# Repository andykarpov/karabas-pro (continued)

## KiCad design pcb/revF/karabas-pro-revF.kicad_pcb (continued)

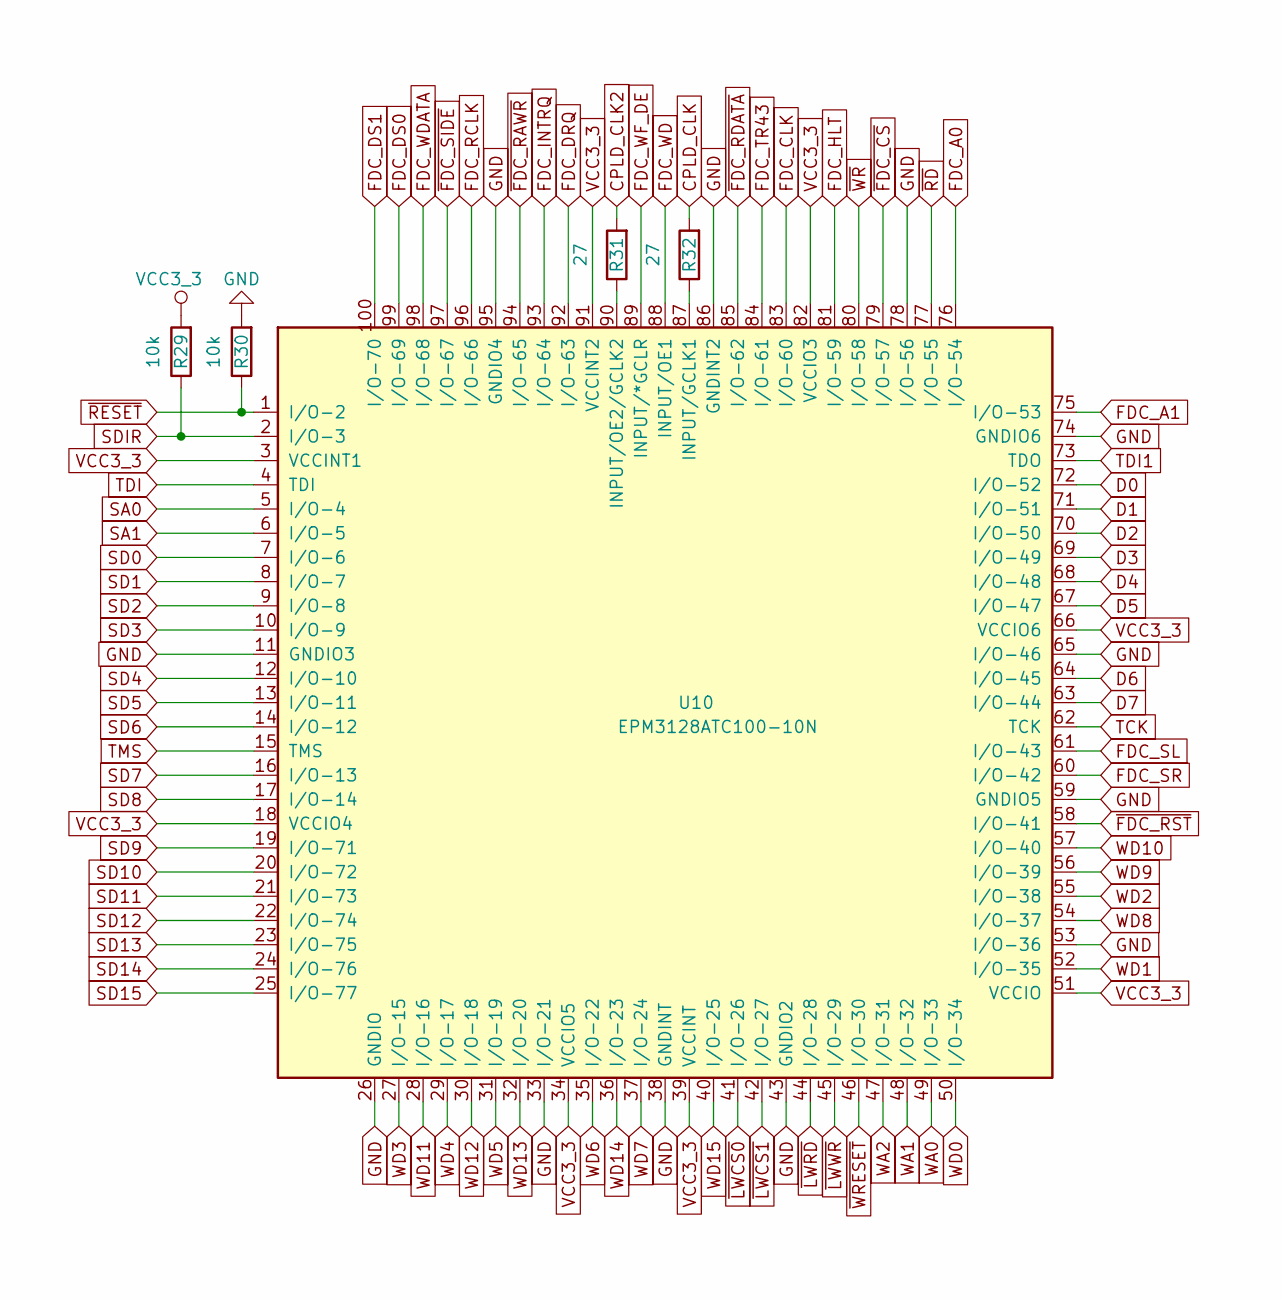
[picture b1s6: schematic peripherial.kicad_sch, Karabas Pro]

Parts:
R29, R30: 10k; R_0805_2012Metric_Pad1.20x1.40mm_HandSolder
R31, R32: 27; R_0805_2012Metric_Pad1.20x1.40mm_HandSolder
U10: EPM3128ATC100-10N; LQFP-100_14x14mm_P0.5mm

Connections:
CPLD_CLK: R32.2; also elsewhere on the board
CPLD_CLK2: R31.2; also elsewhere on the board
D0: U10.72 (I/O-52); also elsewhere on the board
D1: U10.71 (I/O-51); also elsewhere on the board
D2: U10.70 (I/O-50); also elsewhere on the board
D3: U10.69 (I/O-49); also elsewhere on the board
D4: U10.68 (I/O-48); also elsewhere on the board
D5: U10.67 (I/O-47); also elsewhere on the board
D6: U10.64 (I/O-45); also elsewhere on the board
D7: U10.63 (I/O-44); also elsewhere on the board
FDC_A0: U10.76 (I/O-54); also elsewhere on the board
FDC_A1: U10.75 (I/O-53); also elsewhere on the board
FDC_CLK: U10.83 (I/O-60); also elsewhere on the board
FDC_DRQ: U10.92 (I/O-63); also elsewhere on the board
FDC_DS0: U10.99 (I/O-69); also elsewhere on the board
FDC_DS1: U10.100 (I/O-70); also elsewhere on the board
FDC_HLT: U10.81 (I/O-59); also elsewhere on the board
FDC_INTRQ: U10.93 (I/O-64); also elsewhere on the board
FDC_RCLK: U10.96 (I/O-66); also elsewhere on the board
FDC_SL: U10.61 (I/O-43); also elsewhere on the board
FDC_SR: U10.60 (I/O-42); also elsewhere on the board
FDC_TR43: U10.84 (I/O-61); also elsewhere on the board
FDC_WD: U10.88 (INPUT/OE1); also elsewhere on the board
FDC_WDATA: U10.98 (I/O-68); also elsewhere on the board
FDC_WF_DE: U10.89 (INPUT/*GCLR); also elsewhere on the board
GND: R30.2, U10.11 (GNDIO3), U10.26 (GNDIO), U10.33 (I/O-21), U10.38 (GNDINT), U10.43 (GNDIO2), U10.53 (I/O-36), U10.59 (GNDIO5), U10.65 (I/O-46), U10.74 (GNDIO6), U10.78 (I/O-56), U10.86 (GNDINT2), U10.95 (GNDIO4); also elsewhere on the board
unnamed: R32.1, U10.87 (INPUT/GCLK1)
unnamed: R31.1, U10.90 (INPUT/OE2/GCLK2)
SA0: U10.5 (I/O-4); also elsewhere on the board
SA1: U10.6 (I/O-5); also elsewhere on the board
SD0: U10.7 (I/O-6); also elsewhere on the board
SD1: U10.8 (I/O-7); also elsewhere on the board
SD2: U10.9 (I/O-8); also elsewhere on the board
SD3: U10.10 (I/O-9); also elsewhere on the board
SD4: U10.12 (I/O-10); also elsewhere on the board
SD5: U10.13 (I/O-11); also elsewhere on the board
SD6: U10.14 (I/O-12); also elsewhere on the board
SD7: U10.16 (I/O-13); also elsewhere on the board
SD8: U10.17 (I/O-14); also elsewhere on the board
SD9: U10.19 (I/O-71); also elsewhere on the board
SD10: U10.20 (I/O-72); also elsewhere on the board
SD11: U10.21 (I/O-73); also elsewhere on the board
SD12: U10.22 (I/O-74); also elsewhere on the board
SD13: U10.23 (I/O-75); also elsewhere on the board
SD14: U10.24 (I/O-76); also elsewhere on the board
SD15: U10.25 (I/O-77); also elsewhere on the board
SDIR: R29.1, U10.2 (I/O-3); also elsewhere on the board
TCK: U10.62 (TCK); also elsewhere on the board
TDI: U10.4 (TDI); also elsewhere on the board
TDI1: U10.73 (TDO); also elsewhere on the board
TMS: U10.15 (TMS); also elsewhere on the board
VCC3_3: R29.2, U10.3 (VCCINT1), U10.18 (VCCIO4), U10.34 (VCCIO5), U10.39 (VCCINT), U10.51 (VCCIO), U10.66 (VCCIO6), U10.82 (VCCIO3), U10.91 (VCCINT2); also elsewhere on the board
WA0: U10.49 (I/O-33); also elsewhere on the board
WA1: U10.48 (I/O-32); also elsewhere on the board
WA2: U10.47 (I/O-31); also elsewhere on the board
WD0: U10.50 (I/O-34); also elsewhere on the board
WD1: U10.52 (I/O-35); also elsewhere on the board
WD2: U10.55 (I/O-38); also elsewhere on the board
WD3: U10.27 (I/O-15); also elsewhere on the board
WD4: U10.29 (I/O-17); also elsewhere on the board
WD5: U10.31 (I/O-19); also elsewhere on the board
WD6: U10.35 (I/O-22); also elsewhere on the board
WD7: U10.37 (I/O-24); also elsewhere on the board
WD8: U10.54 (I/O-37); also elsewhere on the board
WD9: U10.56 (I/O-39); also elsewhere on the board
WD10: U10.57 (I/O-40); also elsewhere on the board
WD11: U10.28 (I/O-16); also elsewhere on the board
WD12: U10.30 (I/O-18); also elsewhere on the board
WD13: U10.32 (I/O-20); also elsewhere on the board
WD14: U10.36 (I/O-23); also elsewhere on the board
WD15: U10.40 (I/O-25); also elsewhere on the board
~FDC_CS: U10.79 (I/O-57); also elsewhere on the board
~FDC_RAWR: U10.94 (I/O-65); also elsewhere on the board
~FDC_RDATA: U10.85 (I/O-62); also elsewhere on the board
~FDC_RST: U10.58 (I/O-41); also elsewhere on the board
~FDC_SIDE: U10.97 (I/O-67); also elsewhere on the board
~LWCS0: U10.41 (I/O-26); also elsewhere on the board
~LWCS1: U10.42 (I/O-27); also elsewhere on the board
~LWRD: U10.44 (I/O-28); also elsewhere on the board
~LWWR: U10.45 (I/O-29); also elsewhere on the board
~RD: U10.77 (I/O-55); also elsewhere on the board
~RESET: R30.1, U10.1 (I/O-2); also elsewhere on the board
~WRESET: U10.46 (I/O-30); also elsewhere on the board
~WR: U10.80 (I/O-58); also elsewhere on the board

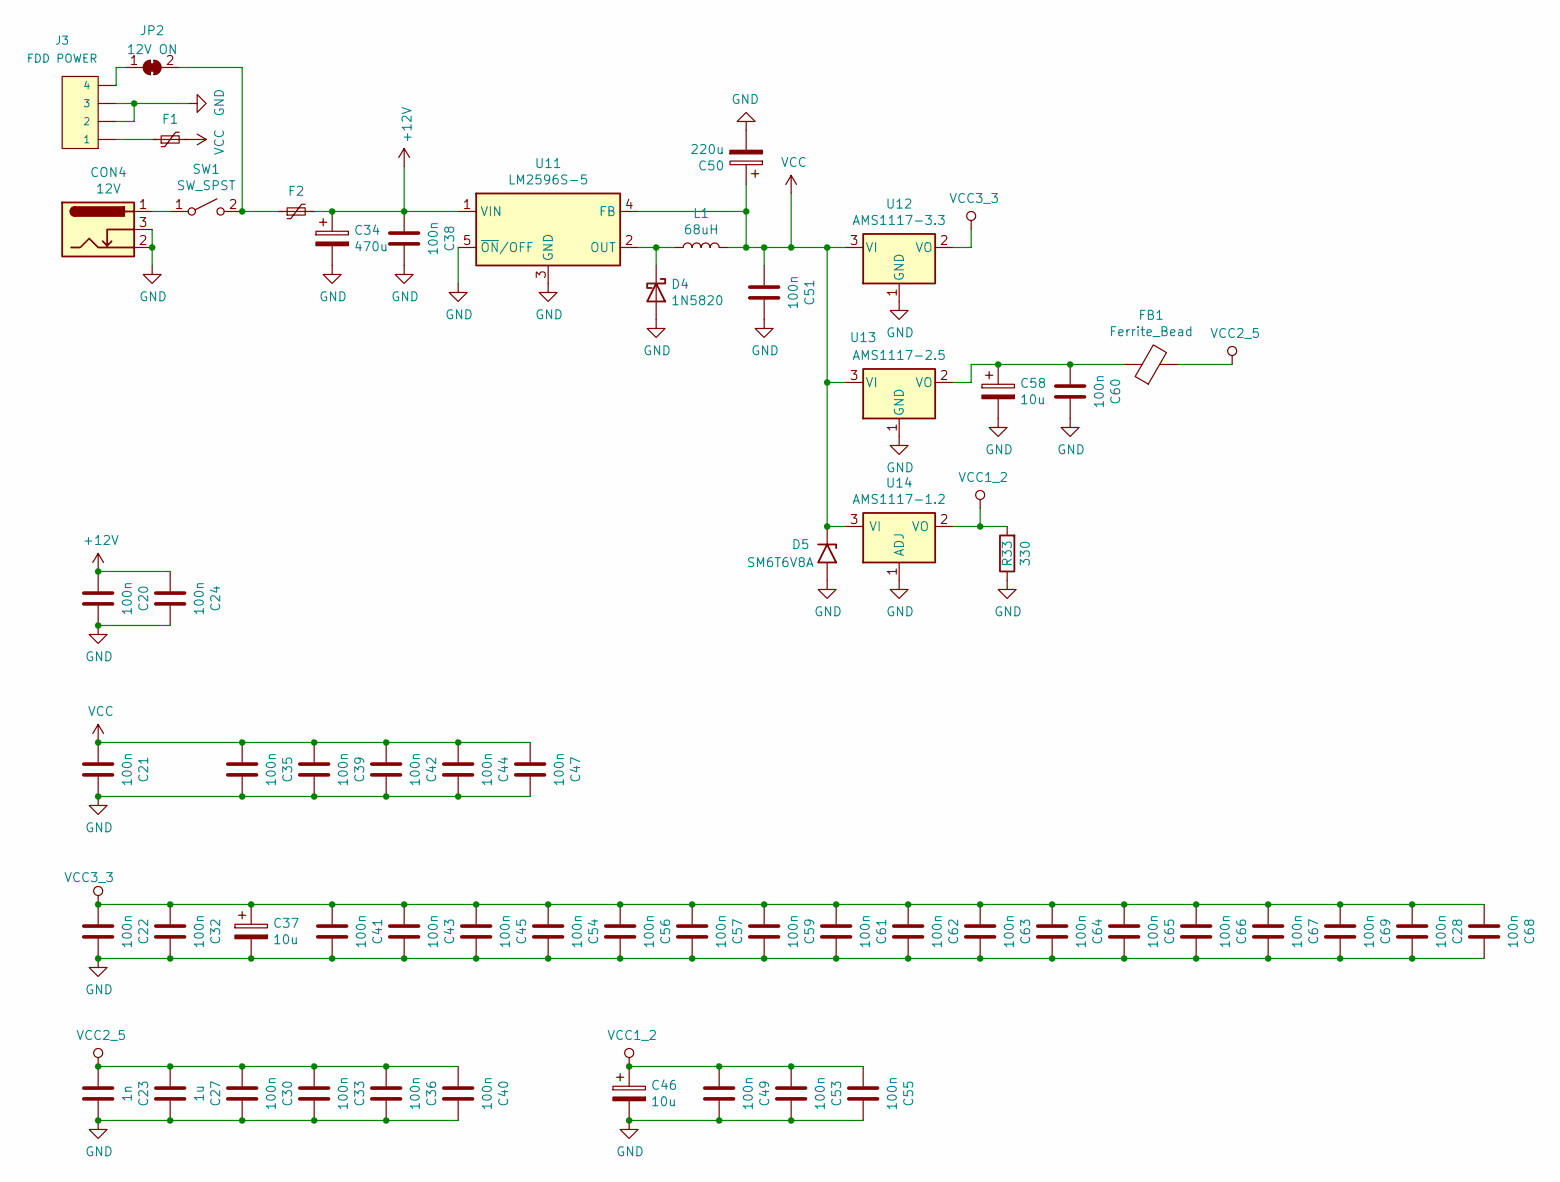
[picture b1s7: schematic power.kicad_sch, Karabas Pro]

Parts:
C20, C21, C22, C24, C28, C30, C32, C33, C35, C36, C38, C39, C40, C41, C42, C43, C44, C45, C47, C49, C51, C53, C54, C55, C56, C57, C59, C60, C61, C62, C63, C64, C65, C66, C67, C68, C69: 100n; C_0805_2012Metric_Pad1.18x1.45mm_HandSolder
C23: 1n; C_0805_2012Metric_Pad1.18x1.45mm_HandSolder
C27: 1u; C_0805_2012Metric_Pad1.18x1.45mm_HandSolder
C34: 470u; CP_Radial_D8.0mm_P3.80mm
C37, C46, C58: 10u; CP_EIA-7343-31_Kemet-D-uni
C50: 220u; CP_Radial_D7.5mm_P2.50mm
CON4: 12V; BarrelJack_Wuerth_6941xx301002
D4: 1N5820; D_DO-201AD_P15.24mm_Horizontal
D5: SM6T6V8A; D_SMB_Handsoldering
F1, F2: Polyfuse_Small; Fuse_1812_4532Metric_Pad1.30x3.40mm_HandSolder
FB1: Ferrite_Bead; L_0805_2012Metric_Pad1.15x1.40mm_HandSolder
J3: FDD POWER; PinHeader_1x04_P2.54mm_Vertical
JP2: 12V ON; SolderJumper-2_P1.3mm_Bridged_Pad1.0x1.5mm
L1: 68uH; L_12x12mm_H6mm
R33: 330; R_0805_2012Metric_Pad1.20x1.40mm_HandSolder
SW1: SW_SPST; SW_Slide_SPDT_Angled_CK_OS102011MA1Q
U11: LM2596S-5; TO-263-5_TabPin3
U12: AMS1117-3.3; TO-252-2
U13: AMS1117-2.5; SOT-223-3_TabPin2
U14: AMS1117-1.2; SOT-223-3_TabPin2

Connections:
+12V: C20.1, C24.1, C34.1, C38.1, F2.2, U11.1 (VIN); also elsewhere on the board
GND: C20.2, C21.2, C22.2, C23.2, C24.2, C27.2, C28.2, C30.2, C32.2, C33.2, C34.2, C35.2, C36.2, C37.2, C38.2, C39.2, C40.2, C41.2, C42.2, C43.2, C44.2, C45.2, C46.2, C47.2, C49.2, C50.2, C51.2, C53.2, C54.2, C55.2, C56.2, C57.2, C58.2, C59.2, C60.2, C61.2, C62.2, C63.2, C64.2, C65.2, C66.2, C67.2, C68.2, C69.2, CON4.2, CON4.3, D4.2 (A), D5.2 (A2), J3.2, J3.3, R33.1, U11.3 (GND), U11.5 (~ON/OFF), U12.1 (GND), U13.1 (GND), U14.1 (ADJ); also elsewhere on the board
unnamed: D4.1 (K), L1.1, U11.2 (OUT)
unnamed: F1.1, J3.1
unnamed: J3.4, JP2.1 (A)
unnamed: F2.1, JP2.2 (B), SW1.2 (B)
unnamed: CON4.1, SW1.1 (A)
unnamed: C58.1, C60.1, FB1.1, U13.2 (VO)
VCC: C21.1, C35.1, C39.1, C42.1, C44.1, C47.1, C50.1, C51.1, D5.1 (A1), F1.2, L1.2, U11.4 (FB), U12.3 (VI), U13.3 (VI), U14.3 (VI); also elsewhere on the board
VCC1_2: C46.1, C49.1, C53.1, C55.1, R33.2, U14.2 (VO); also elsewhere on the board
VCC2_5: C23.1, C27.1, C30.1, C33.1, C36.1, C40.1, FB1.2; also elsewhere on the board
VCC3_3: C22.1, C28.1, C32.1, C37.1, C41.1, C43.1, C45.1, C54.1, C56.1, C57.1, C59.1, C61.1, C62.1, C63.1, C64.1, C65.1, C66.1, C67.1, C68.1, C69.1, U12.2 (VO); also elsewhere on the board

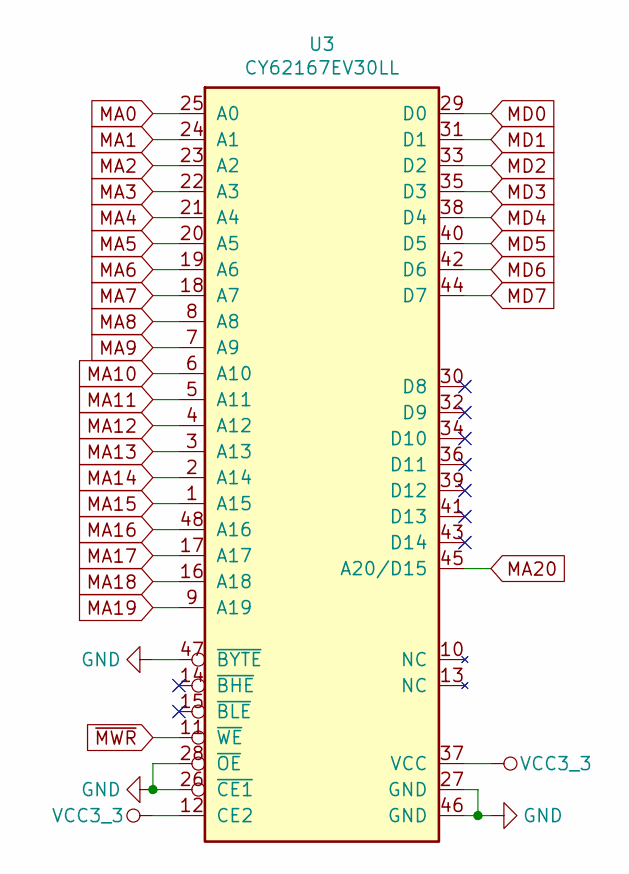
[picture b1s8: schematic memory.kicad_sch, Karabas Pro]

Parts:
U3: CY62167EV30LL; TSOP-I-48_18.4x12mm_P0.5mm

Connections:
GND: U3.26 (~CE1), U3.27 (GND), U3.28 (~OE), U3.46 (GND), U3.47 (~BYTE); also elsewhere on the board
MA0: U3.25 (A0); also elsewhere on the board
MA1: U3.24 (A1); also elsewhere on the board
MA2: U3.23 (A2); also elsewhere on the board
MA3: U3.22 (A3); also elsewhere on the board
MA4: U3.21 (A4); also elsewhere on the board
MA5: U3.20 (A5); also elsewhere on the board
MA6: U3.19 (A6); also elsewhere on the board
MA7: U3.18 (A7); also elsewhere on the board
MA8: U3.8 (A8); also elsewhere on the board
MA9: U3.7 (A9); also elsewhere on the board
MA10: U3.6 (A10); also elsewhere on the board
MA11: U3.5 (A11); also elsewhere on the board
MA12: U3.4 (A12); also elsewhere on the board
MA13: U3.3 (A13); also elsewhere on the board
MA14: U3.2 (A14); also elsewhere on the board
MA15: U3.1 (A15); also elsewhere on the board
MA16: U3.48 (A16); also elsewhere on the board
MA17: U3.17 (A17); also elsewhere on the board
MA18: U3.16 (A18); also elsewhere on the board
MA19: U3.9 (A19); also elsewhere on the board
MA20: U3.45 (A20/D15); also elsewhere on the board
MD0: U3.29 (D0); also elsewhere on the board
MD1: U3.31 (D1); also elsewhere on the board
MD2: U3.33 (D2); also elsewhere on the board
MD3: U3.35 (D3); also elsewhere on the board
MD4: U3.38 (D4); also elsewhere on the board
MD5: U3.40 (D5); also elsewhere on the board
MD6: U3.42 (D6); also elsewhere on the board
MD7: U3.44 (D7); also elsewhere on the board
VCC3_3: U3.12 (CE2), U3.37 (VCC); also elsewhere on the board
~MWR: U3.11 (~WE); also elsewhere on the board

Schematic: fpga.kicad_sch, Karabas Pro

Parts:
J1: FPGA JTAG; IDC-Header_2x05_P2.54mm_Horizontal
R1, R2, R3: 10k; R_0805_2012Metric_Pad1.20x1.40mm_HandSolder
R6, R9, R10: 2k4; R_0805_2012Metric_Pad1.20x1.40mm_HandSolder
R11: 27; R_0805_2012Metric_Pad1.20x1.40mm_HandSolder
U1: EP4CE22E22C8N; ALTERA-QFP-145
X1: 50 MHz; Oscillator_SMD_SeikoEpson_SG8002CA-4Pin_7.0x5.0mm_HandSolde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

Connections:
CLK_50MHZ: R11.2, U1.23 (CLK1)
CONF_DONE: R1.1, U1.92 (CONF_DONE); also elsewhere on the board
CPLD_CLK: U1.113 (IO(PLL2_CLKOUTP)); also elsewhere on the board
CPLD_CLK2: U1.112 (IO(PLL2_CLKOUTN)); also elsewhere on the board
DATA0: U1.13 (IO(DATA0)); also elsewhere on the board
DCLK: U1.12 (IO(DCLK)); also elsewhere on the board
GND: J1.2, J1.10, R9.1, U1.2 (GNDA3), U1.4 (GND), U1.19 (GND), U1.21 (NCE), U1.22 (GND), U1.27 (GND), U1.36 (GNDA1), U1.41 (GND), U1.48 (GND), U1.57 (GND), U1.63 (GND), U1.74 (GNDA4), U1.79 (GND), U1.82 (GND), U1.94 (MSEL0), U1.95 (GND), U1.96 (MSEL1), U1.97 (MSEL2), U1.108 (GNDA2), U1.118 (GND), U1.123 (GND), U1.131 (GND), U1.140 (GND), U1.145 (GND), X1.2 (GND); also elsewhere on the board
LFDC_STEP: U1.55 (CLK12); also elsewhere on the board
LSND_BS: U1.144 (IO); also elsewhere on the board
LSND_DAT: U1.142 (IO); also elsewhere on the board
LSND_WS: U1.143 (IO); also elsewhere on the board
MA0: U1.33 (IO(RDN1)); also elsewhere on the board
MA1: U1.85 (IO); also elsewhere on the board
MA2: U1.83 (IO); also elsewhere on the board
MA3: U1.80 (IO); also elsewhere on the board
MA4: U1.77 (IO(RDN3)); also elsewhere on the board
MA5: U1.76 (IO(RUP3)); also elsewhere on the board
MA6: U1.72 (IO); also elsewhere on the board
MA7: U1.71 (IO); also elsewhere on the board
MA8: U1.65 (IO); also elsewhere on the board
MA9: U1.64 (IO); also elsewhere on the board
MA10: U1.60 (IO); also elsewhere on the board
MA11: U1.59 (IO); also elsewhere on the board
MA12: U1.58 (IO); also elsewhere on the board
MA13: U1.51 (IO); also elsewhere on the board
MA14: U1.50 (IO); also elsewhere on the board
MA15: U1.49 (IO); also elsewhere on the board
MA16: U1.46 (IO); also elsewhere on the board
MA17: U1.69 (IO); also elsewhere on the board
MA18: U1.68 (IO); also elsewhere on the board
MA19: U1.66 (IO(RUP2)); also elsewhere on the board
MA20: U1.44 (IO(PLL1_CLKOUTN)); also elsewhere on the board
MCU_CS: U1.53 (CLK14); also elsewhere on the board
MCU_MISO: U1.86 (IO(DEV_OE)); also elsewhere on the board
MCU_MOSI: U1.52 (CLK15); also elsewhere on the board
MCU_SCK: U1.54 (CLK13); also elsewhere on the board
MD0: U1.32 (IO(RUP1)); also elsewhere on the board
MD1: U1.31 (IO); also elsewhere on the board
MD2: U1.30 (IO); also elsewhere on the board
MD3: U1.28 (IO); also elsewhere on the board
MD4: U1.11 (IO); also elsewhere on the board
MD5: U1.39 (IO); also elsewhere on the board
MD6: U1.42 (IO); also elsewhere on the board
MD7: U1.43 (IO(PLL1_CLKOUTP)); also elsewhere on the board
NCONFIG: R2.1, U1.14 (NCONFIG); also elsewhere on the board
NSTATUS: R3.1, U1.9 (NSTATUS); also elsewhere on the board
unnamed: R11.1, X1.3 (OUT)
SA0: U1.110 (IO); also elsewhere on the board
SA1: U1.106 (IO); also elsewhere on the board
SD0: U1.105 (IO); also elsewhere on the board
SD1: U1.104 (IO); also elsewhere on the board
SD2: U1.103 (IO(CLKUSR)); also elsewhere on the board
SD3: U1.101 (IO(NCE0)); also elsewhere on the board
SD4: U1.100 (IO); also elsewhere on the board
SD5: U1.99 (IO(CRC_ERROR)); also elsewhere on the board
SD6: U1.98 (IO(INIT_DONE)); also elsewhere on the board
SD7: U1.87 (IO(DEV_CLRN)); also elsewhere on the board
SD8: U1.91 (CLK4); also elsewhere on the board
SD9: U1.90 (CLK5); also elsewhere on the board
SD10: U1.89 (CLK6); also elsewhere on the board
SD11: U1.88 (CLK7); also elsewhere on the board
SD12: U1.126 (CLK8); also elsewhere on the board
SD13: U1.127 (CLK9); also elsewhere on the board
SD14: U1.128 (CLK10); also elsewhere on the board
SD15: U1.129 (CLK11); also elsewhere on the board
SDIR: U1.111 (IO); also elsewhere on the board
SD_DI: U1.7 (IO); also elsewhere on the board
SD_SCK: U1.6 (IO(ASDO)); also elsewhere on the board
TAPE_IN: U1.24 (CLK2); also elsewhere on the board
TAPE_OUT: U1.8 (IO(NCSO)); also elsewhere on the board
TCK: J1.1, R9.2, U1.16 (TCK); also elsewhere on the board
TDI: J1.9, R10.1; also elsewhere on the board
TDI1: U1.15 (TDI); also elsewhere on the board
TDO: J1.3, U1.20 (TDO)
TMS: J1.5, R6.1, U1.18 (TMS); also elsewhere on the board
VCC1_2: U1.1 (VCCD_PLL3), U1.5 (VCCINT), U1.29 (VCCINT), U1.34 (VCCINT), U1.37 (VCCD_PLL1), U1.38 (VCCINT), U1.45 (VCCINT), U1.61 (VCCINT), U1.70 (VCCINT), U1.73 (VCCD_PLL4), U1.78 (VCCINT), U1.84 (VCCINT), U1.102 (VCCINT), U1.109 (VCCD_PLL2), U1.116 (VCCINT), U1.124 (VCCINT), U1.134 (VCCINT), U1.138 (VCCINT); also elsewhere on the board
VCC2_5: U1.3 (VCCA3), U1.35 (VCCA1), U1.75 (VCCA4), U1.107 (VCCA2); also elsewhere on the board
VCC3_3: J1.4, R1.2, R2.2, R3.2, R6.2, R10.2, U1.17 (VCCIO1), U1.26 (VCCIO2), U1.40 (VCCIO3), U1.47 (VCCIO3), U1.56 (VCCIO4), U1.62 (VCCIO4), U1.81 (VCCIO5), U1.93 (VCCIO6), U1.117 (VCCIO7), U1.122 (VCCIO7), U1.130 (VCCIO8), U1.139 (VCCIO8), X1.1 (~ST), X1.4 (VCC); also elsewhere on the board
VGA_B0: U1.120 (IO); also elsewhere on the board
VGA_B1: U1.121 (IO); also elsewhere on the board
VGA_B2: U1.125 (IO); also elsewhere on the board
VGA_G0: U1.132 (IO); also elsewhere on the board
VGA_G1: U1.133 (IO); also elsewhere on the board
VGA_G2: U1.135 (IO); also elsewhere on the board
VGA_HS: U1.119 (IO); also elsewhere on the board
VGA_R0: U1.136 (IO); also elsewhere on the board
VGA_R1: U1.137 (IO); also elsewhere on the board
VGA_R2: U1.141 (IO); also elsewhere on the board
VGA_VS: U1.115 (IO(RDN4)); also elsewhere on the board
~MCU_SD_CS: U1.25 (CLK3); also elsewhere on the board
~MWR: U1.67 (IO(RDN2)); also elsewhere on the board
~RESET: U1.114 (IO(RUP4)); also elsewhere on the board
~SD_CS: U1.10 (IO); also elsewhere on the board

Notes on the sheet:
JTAG
Clock

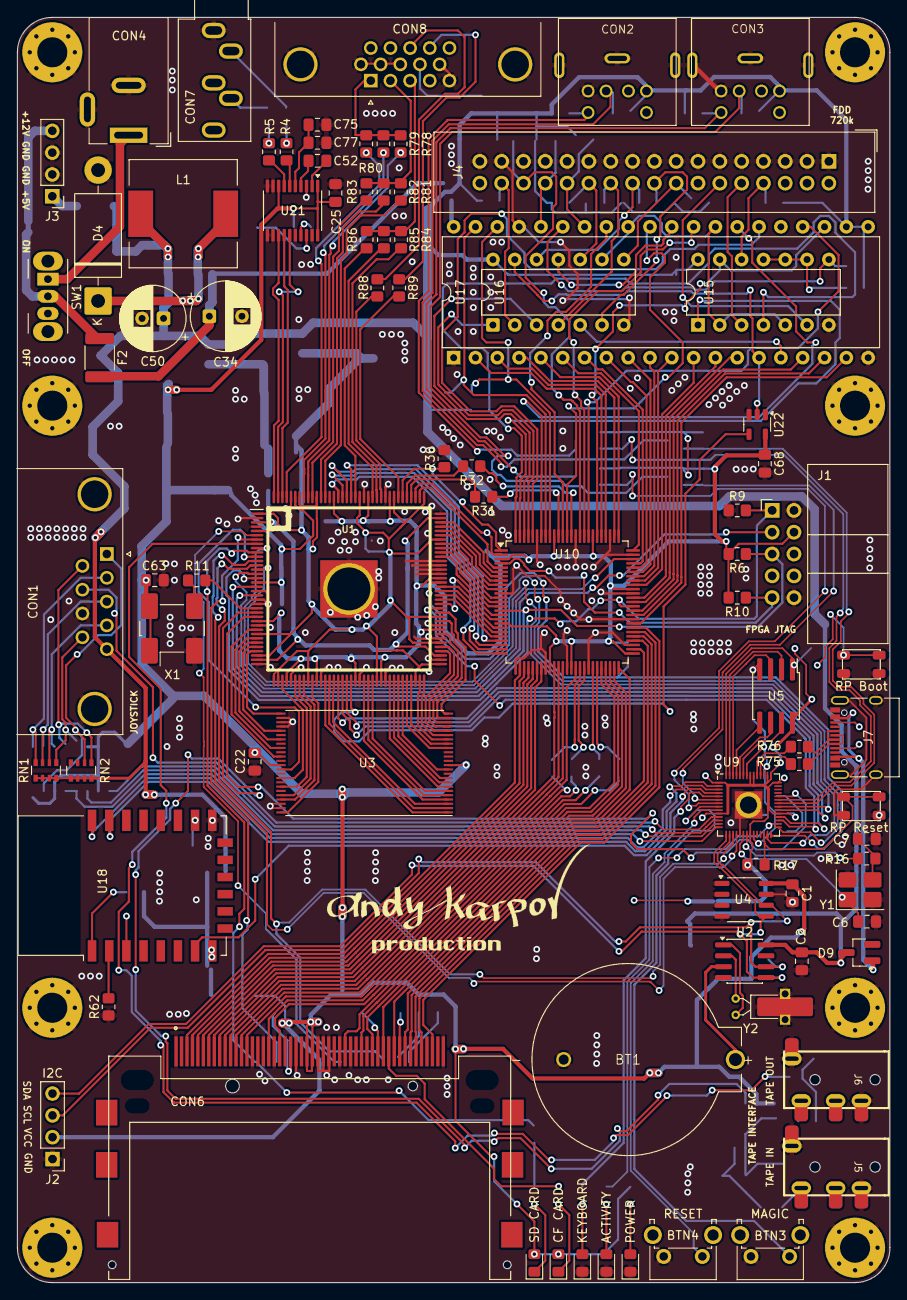
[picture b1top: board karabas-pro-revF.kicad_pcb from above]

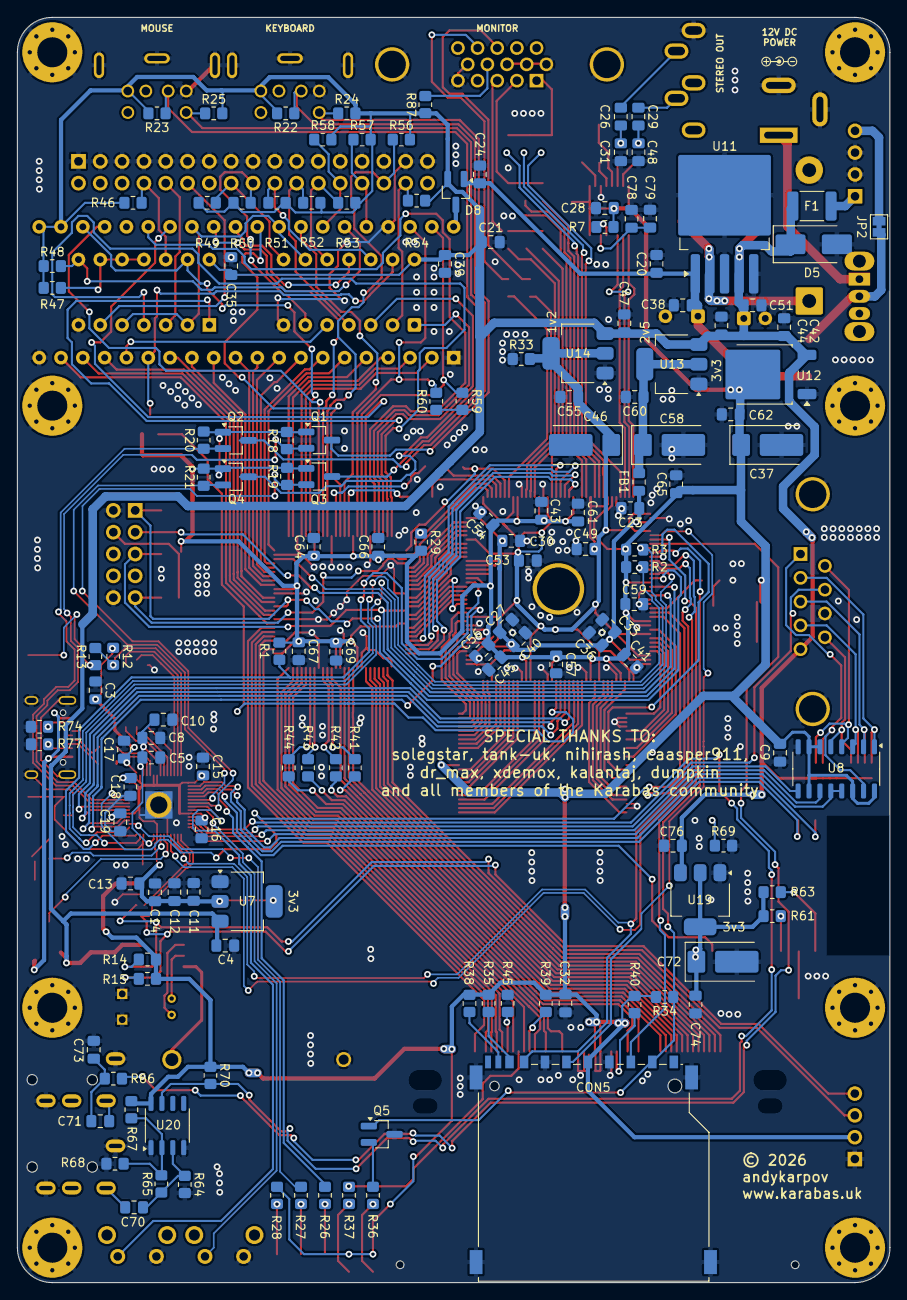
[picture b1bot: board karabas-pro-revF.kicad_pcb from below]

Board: 2 copper layers, 101.6 x 147.3 mm, 240 parts (145 on the bottom side), 268 nets.

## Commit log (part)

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2021-11-22 reverted UART2 CTS on PIN_138
2021-11-22 Build 21112221
2021-11-22 Build 21112222
2021-11-23 fixed "turbo mode" async off
2021-11-25 Xm hz (#72)
    * added wait signal logic
    * x3 stable turbo mode
    * reverted UART2 CTS on PIN_138
    * Build 21112221
    * Removed outdated files
    * Build 21112222
2021-12-01 added NMI button in Profi Mode
2021-12-06 first memory config ports init
2021-12-07 added lck128 bits
2021-12-15 added 108b...138b, 218b port to memory module
2021-12-17 added port corrections to 7FFD
2021-12-18 Build v21121823
2021-12-20 added ROM pages selection by Page0(4:0) reg.
2021-12-21 added Page0-Page3
2021-12-22 added SCO and SCR bits to MemConfig
2021-12-24 Revert "refactored all with new mapper"
    This reverts commit 70f7907ce01bb459284be150f4c713495867ce6d.
2021-12-24 new mode
2021-12-27 new turbo mode selector
2021-12-27 new turbo mode selector (#74)
2021-12-27 Added bank send/receive cmd while xchanging with FPGA
2021-12-27 Added bank send/receive cmd while handling rtc address
2021-12-28 new rom page
2021-12-28 added temp.sync for cpu_pages
2021-12-28 Refactored fpga side for the new SPI protocol
2021-12-28 New experimental build with new SPI protocol and support for 256 bytes eeprom
2021-12-28 Adopted RK86 core with new AVR SPI protocol
2021-12-28 New pong core build with new AVR SPI protocol
2021-12-29 some fixes
2022-03-09 Added VPages for Spec and Profi modes
2022-03-15 Rtc 256 bytes (#75)
    * Added bank send/receive cmd while xchanging with FPGA
    * Added bank send/receive cmd while handling rtc address
    * New AVR and FPGA build with 256 bytes EEPROM
    * Refactored AVR protocol from 2 to 3 byte sequence
    * Refactored fpga side for the new SPI protocol
    * New experimental build with new SPI protocol and support for 256 bytes eeprom
2022-03-15 Readme українською
2022-03-17 updated gerbers
2022-03-21 Fixed rev.EU
2022-05-03 Fixed cursor keys (removed delayed CS)
2022-05-03 Updated FPGA images with new testROM by Dr.Max
2022-05-03 Added Qiwi walled of Dr.Max
2022-05-03 Updated info about Dr.Max
2022-05-05 Fixed CAPS key presses/releases
2022-05-05 AVR release 22050601
2022-05-05 Added gitignore
2022-05-05 misc changes
2022-05-15 ROMain v0.5
2022-05-15 Build with updated ROMain to v0.5
2022-05-23 ROMain 0.52
2022-05-23 FPGA build 22052319
2022-06-23 FPGA build v22062315 + AVR build v22062223
    New release with ukrainian and russian OSD menu
2022-06-23 Cyrillic OSD menu (#77)
    FPGA build v22062315 + AVR build v22062223
2022-06-23 Build v22062316
2022-06-23 Build v22062316 (#78)
    Added OSD icons on the border for FDD, SD, CF card activity
2022-06-23 Build v22062318
2022-06-23 Centered OSD position 24px down vertically for the profi screen
2022-06-23 FPGA build v22062400
2022-07-24 latest changes
2022-07-24 New build with fixed typo in english translations
2022-12-29 ROMain v1.02
2022-12-29 Fatall
2022-12-29 Updated JICs with ROMain v1.02
2022-12-30 Updated release with ROMain v1.03
2022-12-30 Textual changes
2023-01-02 Dev docs, preview
2023-01-03 Документация разработчика v1.0
2023-01-07 Downgraded the latest FPGA build to 22062318, updated ROMain to v1.03
2023-04-19 Reverted OSD icons, reverted ROMain to the version with embedded Fatall
2023-04-29 Fixed Rev.E 6MB memory access via port 7ffd bits 6,7
2023-04-29 Добавлена опция отключаемых иконок OSD
2023-04-29 need to fix OSD icons.
2023-04-29 Dev build with memconfig
2023-04-30 new zifi state machine, fixed reset
2023-04-30 Added 4kb rx fifo for zifi
2023-04-30 Added WGET support for ZiFi
2023-04-30 Удаление версии netman под karabas-pro в пользу оригинального репозитария nihirash
2023-04-30 Добавлен readme
2023-04-30 Добавлены сборки netman и ugophy под ZiFi UART, обновлены readme
2023-05-02 uGophy for profi hires screen 512x240
2023-05-05 Initial working version of the weather report
2023-05-06 Added weather report release
2023-05-06 removed weather server draft
2023-05-21 Initial version of air alerts map
2023-05-21 Removed status fetch
2023-05-21 Updated alerts build
2023-05-21 Добавлена загрузка картинок под профи экран
2023-06-28 ROMain 2.0
2023-06-28 Updated jics with ROMain 2.0
2023-06-28 Zifi (#81)
    * ZIFI WIP
    * new zifi state machine, fixed reset
    * Added 4kb rx fifo for zifi
    * Moon Rabbit ZiFi support
    * Added WGET support for ZiFi
    * Удаление версии netman под karabas-pro в пользу оригинального репозитария nihirash
2023-06-28 FPGA build 23062900
2023-07-07 Added joy mode selector on AVR side
2023-07-07 Added joy mode support on fpga side
2023-07-07 Build 23070719
2023-07-07 Hotfix
2023-07-08 Added DivMMC menu item into OSD menu
2023-07-08 Added signal divmmc_en from avr
2023-07-09 avr firmware build with divmmc switch
2023-07-09 Fix mistake is_romDIVMMC and is_ramDIVMMC
2023-07-10 Working version, but with glitches
    rombanks can't be switched, divmmc always enabled, garbage on the screen when Divmmc read/write memory (?)
2023-07-10 DIVMMC mapping hooks reworked, NMI DIVMMC implemented
    ZC and DIVMMC work without switching (tested), NMI work correctly
    The screen debris is still present when DIVMMC is running (reading/writing DIVMMC memory), but when I make changes to avoid this, the memory bus timings get messed up.
2023-07-11 Almoust almoust done
    no glitches on screen, cpm working , rom banks switching, DIVMMC on/of menu entry not workig - use COVOX on/of to enable /disable DIVMMC
    still need to test
2023-07-11 Menu fix
    not tested
2023-07-11 Divmmc (#85)
    * Merge changes from local repo
    * divmmc -> divmmc_en
    * Fix mistake is_romDIVMMC and is_ramDIVMMC
    * Implementation of memory logic and DIVMMC dhanged
    divmmc on/off logic removed , temporary only B48 rompage can be used
    not tested
2023-07-11 Fixed 10th byte transfer
2023-07-11 Renamed DIVMMC_EN signal, code cleanup
2023-07-11 Fixed NMI for non-divmmc, added some code cleanup
2023-07-11 AVR build 23071119
2023-07-11 Port 1F disabled on non-kempston joy mode
2023-07-11 DivMMC (#86)
    * Added DivMMC menu item into OSD menu
    * Added signal divmmc_en from avr
    * avr firmware build with divmmc switch
    * Divmmc (#85)
    * Merge changes from local repo
    * divmmc -> divmmc_en
2023-07-12 quick fix Divmmc not start issue in classic videomode
    stopping CPU clk cause error on DIVMMC io or mem operations (and maybe affect io or mem operations with other hardware, i don't lookd deeper)
2023-07-18 RTC.SYS for ESXDOS (karabas-pro RTC standard)
2023-07-21 Added NemoIDE menu item, rearranged main menu
2023-07-21 AVR build 22072122
2023-07-22 Fixed FatAll hobeta to start from ROMain
2023-07-22 Updated latest release 23071119 with ROMain without FatAll
2023-07-24 toCPLD_NEMO_EBL signal added
2023-07-24 SDIR logic changed, new pin 2 name assigned in CLPD
2023-07-24 Nemo HDD signals added to main module
2023-07-24 Bus to CPLD signals added
2023-07-24 change decoding of #FE and #FD ports when Nemo enabled
2023-07-24 nemo_ebl_n to CPLD
2023-07-24 Blink led, OSD when nemo accessed
2023-07-24 for compatibility with old CPLD
    this CPLD was compiled before sources are lost
2023-07-24 Implement CPLD part of nemo HDD inteface
2023-07-25 Turbo off in trdos, not contend memory and ports in turbo
2023-08-28 SDIR pin
2023-08-28 isdos image added (for nemoide)
2023-08-29 Nemoidefinal (#93)
    * toCPLD_NEMO_EBL signal added
    * SDIR commented
    * SDIR logic changed, new pin 2 name assigned in CLPD
    * Nemo HDD signals added to main module
    * Added signals bus_port module
    * Bus to CPLD signals added
2023-08-29 Build 23082919
2023-08-31 Nemoide (#94)
    * Added NemoIDE menu item, rearranged main menu
    * Added nemoide_en flag to the avr module
    * AVR build 22072122
    * Nemoidefinal (#93)
    * toCPLD_NEMO_EBL signal added
    * SDIR commented
2023-09-02 Fixed ctrl+alt+key alt freezing
2023-09-02 AVR build 23090220
2023-09-02 Reduced translations
2023-09-02 Try to re-init mouse forever every 500us
2023-09-02 FPGA build v23090222
2023-09-02 reduced number of mouse init tries
2023-09-04 reduced translations to fit the firmware
2023-09-05 fdd swap fix
    the first time I did swapping of fdd by inverting bit 0 of the FF port, but then I changed it to a more accurate disk number with two bits, who knows, maybe someone wants to implement more than two f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
2023-09-06 Turbo fix (#104)
    * fdd swap fix
    the first time I did swapping of fdd by inverting bit 0 of the FF port, but then I changed it to a more accurate disk number with two bits, who knows, maybe someone wants to implement more than two f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
    * fix issues in turbo mode
    now turbo work correctly in divmmc, in pqdos - turbo disabled only when trdos active
2023-09-06 Build v23090608
2023-09-06 Build 23090619
2023-09-07 Updated PQ-DOS bios to the latest release 0.40
2023-09-15 HW buttons refactoring
2023-09-15 AVR build 23091523
2023-10-20 AVR Build 23102010
2023-10-23 stable ula 128
2023-11-11 one more stable ula 128
2023-11-12 mostly final ula 128
2023-11-13 99% again
2023-11-13 return pause
2023-11-15 14 mhz no wait
2023-11-15 14 mhz TRDOS 'hack', contention issues 'hacked'
2023-11-16 commented signaltap
2023-11-16 Reverted default flags
2023-11-16 AVR build 23111622
2023-11-17 darklite scroll artefacts fix (IN COLOR 128 demo)
2023-11-17 Added +3E mode, renamed Screen to Mode
2023-11-17 Updated AVR build 23111723
2023-11-18 FPGA build 23111818
2023-11-18 Reverted clk_ctrl2
2023-11-18 FPGA build 23111818 #2
2023-11-18 ep4ce6 binary files
2023-12-10 updated donations page
2024-01-18 fdd fix
    fdd fixed in turbo mode 2x/4x
    fdd controller refactored
    WF/DE pin is NC now
2024-01-25 pq-dos bios update to ver.0.41a
2024-01-25 bios pq-dos ROM revert to ver.0.41
2024-04-08 added cof and jic files for ep3c10 rev.E
2024-04-21 Updated ep3c10 build files
2024-05-03 New schematics / revF
2024-05-23 added support MISTer SCART cable
2024-08-11 revF wip
2024-08-11 Updated FDImage v0.87
2024-08-12 ep4ce6 sof updated
    ep4ce6 sof updated
2024-08-13 Updated ep4ce6 jics with FDImage 0.87
2025-02-09 AVR Build 25020913
2025-02-09 Нижняя часть корпуса с круглыми отверстиями 1мм под светодиоды и без поддержек для слотов
2025-02-09 Build 25020915
2025-02-09 Reintroduced fdd_wait
2025-02-09 AVR Build 25020920
2025-02-09 Fixed HW buttons
2025-02-09 Updated T80 CPU
2025-02-09 Updated T80 (Sorgelig)
2025-02-09 Invert TAPE_IN
2025-02-09 FPGA build 25020922
2025-02-10 Removed restriction
2025-02-10 FPGA Build 25021001
2025-06-17 DRC passed
2025-06-17 Updated revF hw and docs
2025-08-17 rp2040 wip
2025-08-17 build script and release folder for rp2040
2025-09-21 RevF pcb
2025-09-21 revF core struct
2025-09-24 Refactored revF alpha2
2025-09-24 Boot core for Karabas Pro revF, initial version
2025-09-24 Fixed SRAM_WR_N signal, improved make process
2025-09-24 fix uart and zifi in turbo mode x2 x4 (#113)
    The UART code was taken and adapted from the latest Spectrum ZXUNO kernel. The behavior of rts(cts) was corrected so that it (and the RX state machine) remain inactive until the Z80 reads an incoming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
2025-09-24 Updated ROMain to v2.71
2025-09-24 Build 25092420
2025-09-24 Added autogeneration of the boot_core.c file from the boot.kg1 core
2025-09-25 Added osd font conversion to the build script
2025-09-30 ROMain 2.8
2025-09-30 Updated release 25092420 with ROMain 2.8
2025-09-30 Updated release 25092420 with ROMain 2.81
2025-10-07 Profi core, WIP
2025-10-11 Boot core, first working version
2025-10-11 Fixed firmware, WIP
2025-10-11 Profi core for revF, WIP
2025-10-11 Updated PCB changelog
2025-10-11 Added chg and log to gitignore
2025-10-13 rp2040 firmware
2025-10-31 Updated latest release with ROMain 2.9
2025-11-03 ROMain v2.91
2026-02-15 current working tree
2026-02-15 ROMain v2.92
2026-02-15 Rebuild jic with latest ROMs
2026-02-15 Dev manual v1.01
2026-02-22 Profi test build on ep4ce22
2026-02-22 Added support for RX FIFO status on FPGA side
2026-02-22 Updated rp2040 build
2026-02-22 cores for ep4ce22
2026-02-23 minor pcb revF fixes
2026-02-23 PCB revF a4
2026-02-23 Updated profi release for ep4ce22
2026-02-23 Updated makefile for ep4ce22
2026-02-24 Fixed osd icons
2026-03-05 cleanup
2026-03-06 Fixed OSD font, osd frame, file loader functionality
2026-03-06 FPGA nes core
2026-03-06 nes core release
2026-03-06 rp2040 build
2026-03-07 Reverted zifi and spi master from the upstream
2026-03-07 Small changes to boot core
2026-03-07 Uncommited changes
